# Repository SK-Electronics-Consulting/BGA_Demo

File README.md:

# BGA Demo

This project is a sandbox-type project with the intention of finding the limitations
and edges of using cheap PCB manufucturing for BGA chips.

Cheap PCB manufacturing in this case are the vendors who provide very inexpensive
PCB fabrication and assembly services, such as JLCPCB and PCBWay.  

The specific goals of this project are:

1. Determine what manufacturing capability is needed for each example BGA. This includes
trace width and spacing, using blind/buried vias, and so on.  
1. Document the costs and turn around times. This may or may not include using
alternates or already in-stock parts (JLC, I'm looking at you!).

## Assumptions

1. Through hole components will be not populated.
1. Only top layer will be populated. Placing components on both sides increases cost. The types of projects that would require BGAs and double sided placement, would also really require a deeper CM relationship than what JLC/PCBWay provide.

## Scope

Items that are out of scope for this project:

1. Unrelated costs and delays, such as delays due to Lunar New Year or parts that are exceptionally difficult to source.

## Versions

### [STM32L431CCY](https://www.st.com/resource/en/datasheet/stm32l431cc.pdf)

This is a WLCSP49 package, 3.1x3.1mm, 0.4mm pitch chip.

#### March 2024 order

* 4-layer board, non-HDI.
* Trace/Space: 0.076mm (0.003")
* Vias 0.25mm w/ 0.15mm hole
* Via in pad was needed
* Smallest Passive is 0402.
* Ordered from JLCPCB on 2024/03/19, delivered on 2024/03/28
* Cost: $255.01
* Mostly just a demo board for the chip. Included a CAN PHY as that's been needed for some projects recently.
* Omitted all through hole components.
* TODO: Actually make the board based on ST's recommendation.  (I rushed ordering it, so I might have missed something crucial and this board be a dud.)
* TODO: Add a Tag-Connect to avoid the 10-pin connector.
* TODO: (Not related to this experiment) Add a 24V to 3.3V SMPS.
* TODO: Try making this with 0.0035" traces, as that seems to be a cost-adder-threshold for JLC.
* Not all balls were able to be exposed in the fanout.  In this design 8 of 49 were left unconnected. A couple of those 8 could easily be brought out, but definitely not all 49 in this fab. See (#learnings) #1.

## Learnings

1. To get a 7x7 grid out completely, you would need blind vias at a minimum, if not a 2+N(+2) stackup. This is because if you look at the 4th (middle) row, you'd fan out this way: `[Top, Blind to In1, Through to In2 or Bottom, (TBD??), Through to In2 or Bottom, Blind to In1, Top]`

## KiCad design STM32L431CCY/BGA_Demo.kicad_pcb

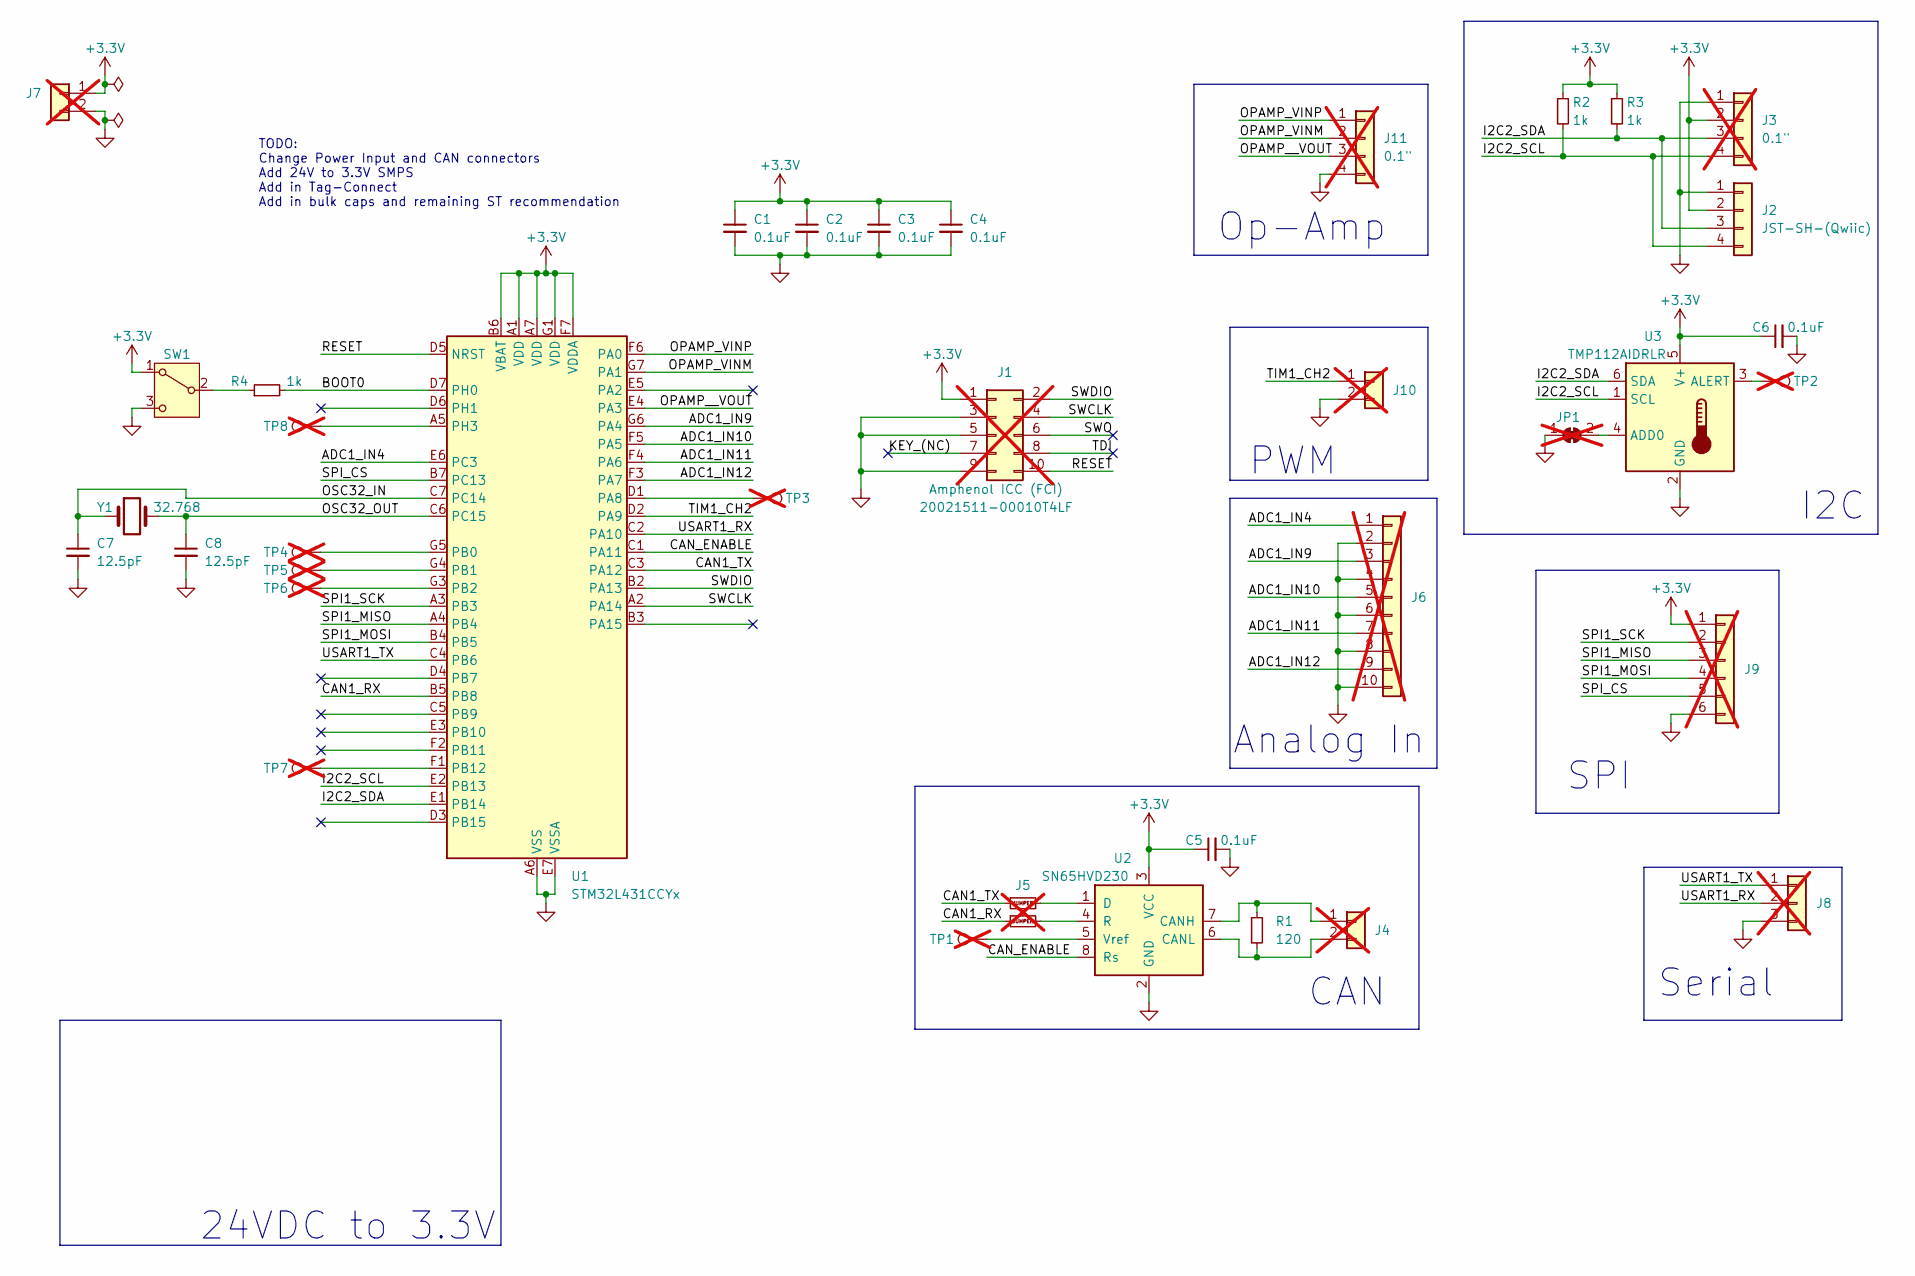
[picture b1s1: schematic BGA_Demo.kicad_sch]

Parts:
C1, C2, C3, C4, C5, C6: 0.1uF; C_0402_1005Metric_Pad0.74x0.62mm_HandSolder; Part Num CC0402KRX7R7BB104; LCSC Part # C60474
C7, C8: 12.5pF; C_0402_1005Metric; Part Num CC0402JRNPO9BN120; LCSC Part # C106201
J1: Conn_02x05_Odd_Even; PinHeader_2x05_P1.27mm_Vertical; Part Num 20021511-00010T4LF; not fitted
J2: JST-SH-(Qwiic); JST_SH_SM04B-SRSS-TB_1x04-1MP_P1.00mm_Horizontal; Part Num SM04B-SRSS-TB(LF)(SN); LCSC Part # C160404
J3, J11: 0.1"; PinHeader_1x04_P2.54mm_Vertical; not fitted
J4, J7, J10: Conn_01x02; PinHeader_1x02_P2.54mm_Vertical; not fitted
J5: RX_TX_Swap; RX_TX_SWAP_0402; not fitted
J6: Conn_01x10; PinHeader_1x10_P2.54mm_Vertical; not fitted
J8: Conn_01x03; PinHeader_1x03_P2.54mm_Vertical; not fitted
J9: Conn_01x06; PinHeader_1x06_P2.54mm_Vertical; not fitted
JP1: SolderJumper_2_Bridged; SolderJumper-2_P1.3mm_Bridged_Pad1.0x1.5mm; not fitted
R1: 120; R_0603_1608Metric_Pad0.98x0.95mm_HandSolder; Part Num AC0603FR-07120RL; LCSC Part # C125925
R2, R3, R4: 1k; R_0402_1005Metric; Part Num RC0402FR-071KL; LCSC Part # C106235
SW1: SW_SPDT; SW_SPDT_CK_JS102011SAQN; Part Num JS102011SAQN; LCSC C221660
TP1: TestPoint; TestPoint_Keystone_5010-5014_Multipurpose; not fitted
TP2, TP3, TP4, TP5, TP6, TP7, TP8: TestPoint; TestPoint_Pad_1.0x1.0mm; not fitted
U1: STM32L431CCYx; ST_WLCSP-49_Die435
U2: SN65HVD230; SOIC-8_3.9x4.9mm_P1.27mm; Part Num SN65HVD230DR; LCSC Part # C12084
U3: TMP112AIDRLR; SOT-563; LCSC C28927
Y1: 32.768; Crystal_SMD_3215-2Pin_3.2x1.5mm; Part Num H31003271C2070CY; LCSC C5361379

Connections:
+3.3V: C1.1, C2.1, C3.1, C4.1, C5.1, C6.1, J1.1, J2.2, J3.2, J7.1, J9.1, R2.1, R3.1, SW1.1 (A), U1.A1 (VDD), U1.A7 (VDD), U1.B6 (VBAT), U1.F7 (VDDA), U1.G1 (VDD), U2.3 (VCC), U3.5 (V+)
/ADC1_IN4: J6.1, U1.E6 (PC3)
/ADC1_IN9: J6.3, U1.G6 (PA4)
/ADC1_IN10: J6.5, U1.F5 (PA5)
/ADC1_IN11: J6.7, U1.F4 (PA6)
/ADC1_IN12: J6.9, U1.F3 (PA7)
/BOOT0: R4.2, U1.D7 (PH0)
/CAN1_RX: J5.1B, U1.B5 (PB8)
/CAN1_TX: J5.1A, U1.C3 (PA12)
/CAN_ENABLE: U1.C1 (PA11), U2.8 (Rs)
/I2C2_SCL: J2.4, J3.4, R2.2, U1.E2 (PB13), U3.1 (SCL)
/I2C2_SDA: J2.3, J3.3, R3.2, U1.E1 (PB14), U3.6 (SDA)
/KEY_(NC): J1.7
/OPAMP_VINM: J11.2, U1.G7 (PA1)
/OPAMP_VINP: J11.1, U1.F6 (PA0)
/OPAMP__VOUT: J11.3, U1.E4 (PA3)
/OSC32_IN: C7.1, U1.C7 (PC14), Y1.1
/OSC32_OUT: C8.1, U1.C6 (PC15), Y1.2
/RESET: J1.10, U1.D5 (NRST)
/SPI1_MISO: J9.3, U1.A4 (PB4)
/SPI1_MOSI: J9.4, U1.B4 (PB5)
/SPI1_SCK: J9.2, U1.A3 (PB3)
/SPI_CS: J9.5, U1.B7 (PC13)
/SWCLK: J1.4, U1.A2 (PA14)
/SWDIO: J1.2, U1.B2 (PA13)
/SWO: J1.6
/TDI: J1.8
/TIM1_CH2: J10.1, U1.D2 (PA9)
/USART1_RX: J8.2, U1.C2 (PA10)
/USART1_TX: J8.1, U1.C4 (PB6)
GND: C1.2, C2.2, C3.2, C4.2, C5.2, C6.2, C7.2, C8.2, J1.3, J1.5, J1.9, J2.1, J3.1, J6.2, J6.4, J6.6, J6.8, J6.10, J7.2, J8.3, J9.6, J10.2, J11.4, JP1.1 (A), SW1.3 (C), U1.A6 (VSS), U1.B1 (VSS), U1.E7 (VSSA), U1.G2 (VSS), U2.2 (GND), U3.2 (GND)
unnamed: J4.1, R1.1, U2.7 (CANH)
unnamed: J4.2, R1.2, U2.6 (CANL)
unnamed: JP1.2 (B), U3.4 (ADD0)
unnamed: R4.1, SW1.2 (B)
unnamed: TP3.1, U1.D1 (PA8)
unnamed: TP4.1, U1.G5 (PB0)
unnamed: TP5.1, U1.G4 (PB1)
unnamed: TP6.1, U1.G3 (PB2)
unnamed: TP7.1, U1.F1 (PB12)
unnamed: TP8.1, U1.A5 (PH3)
unnamed: J5.2A, U2.1 (D)
unnamed: J5.2B, U2.4 (R)
unnamed: TP1.1, U2.5 (Vref)
unnamed: TP2.1, U3.3 (ALERT)

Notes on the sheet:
TODO: Change Power Input and CAN connectors Add 24V to 3.3V SMPS Add in Tag-Connect Add in bulk caps and remaining ST recommendation
24VDC to 3.3V
PWM
Analog In
Op-Amp
SPI
CAN
I2C
Serial

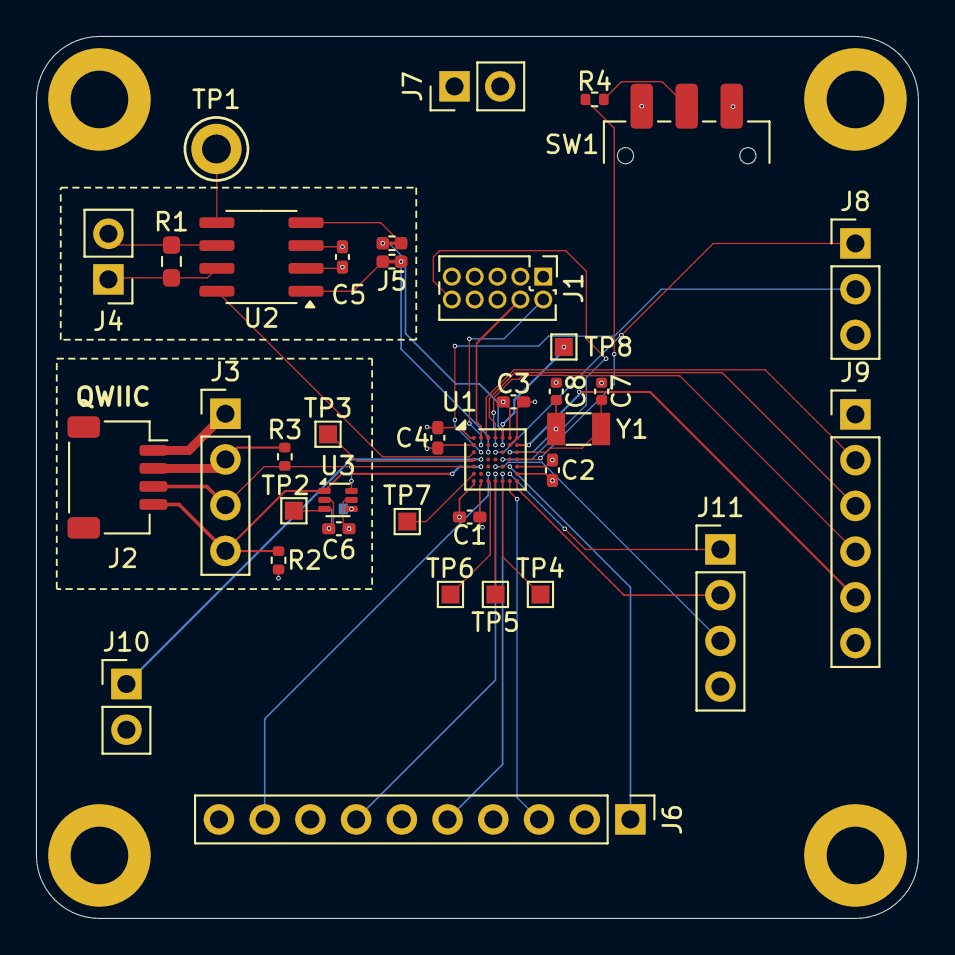
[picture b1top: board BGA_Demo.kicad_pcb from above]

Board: 4 copper layers, 49.0 x 49.0 mm, 37 parts (1 on the bottom side), 42 nets.

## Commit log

2024-03-26 Add gitignore
2024-03-26 JLC Order of STM32L431, March 2024
2024-03-26 Updates to README
